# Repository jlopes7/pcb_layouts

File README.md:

# pcb_layouts
FOSS PCB Based layouts

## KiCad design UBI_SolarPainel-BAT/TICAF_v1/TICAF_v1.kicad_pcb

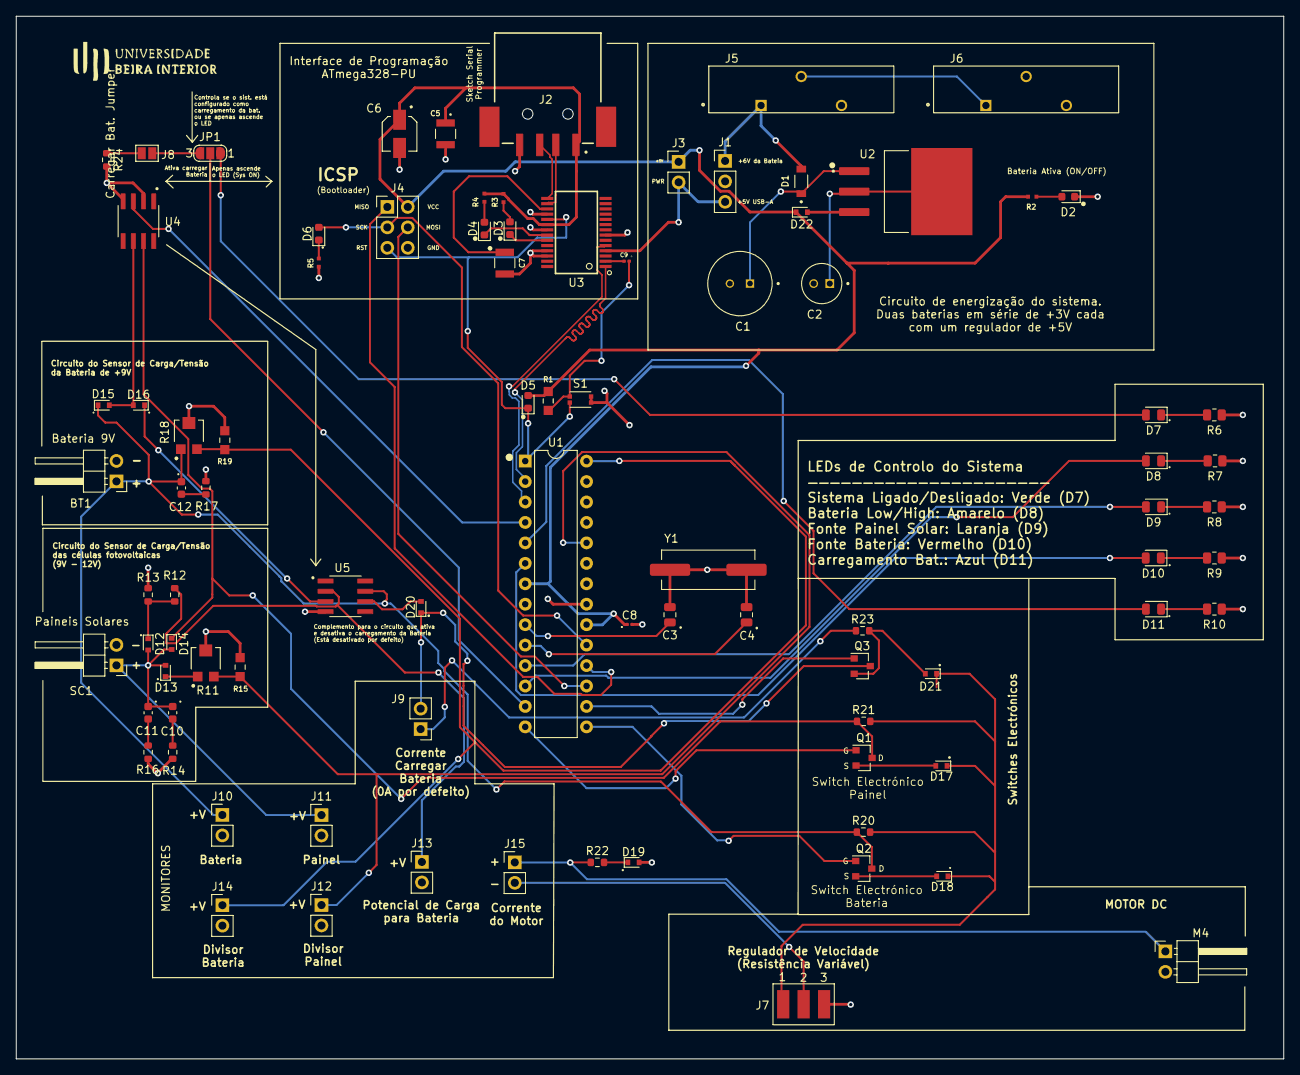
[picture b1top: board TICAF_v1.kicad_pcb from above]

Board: 2 copper layers, 157.5 x 129.5 mm, 87 parts (0 on the bottom side), 67 nets.

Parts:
BT1: Bateria 9V; PinHeader_1x02_P2.54mm_Horizontal
C1: 100u; CAPPRD250W45D800H500
C2: 27u; CAPPRD200W50D500H1100
C3, C4: 22p; C_0805_2012Metric
C5, C7: 0.1u; CAP_ECHU1C104GX5
C6: 10u; CAP_EEEFN0J100R
C8, C9: 100n; C_0201_0603Metric
C10, C12: 10u; C_0603_1608Metric
C11: 22u; C_0603_1608Metric
D1: RB160MM-30TR; DIO_RB160MM-30TR
D2, D3, D4, D6: LED; LED_0603_1608Metric
D5: DIODE; LED_0603_1608Metric
D7: Verde; LED_0805_2012Metric
D8: Amarelo; LED_0805_2012Metric
D9: Laranja; LED_0805_2012Metric
D10: Vermelho; LED_0805_2012Metric
D11: Azul; LED_0805_2012Metric
D12, D13, D14, D15, D16, D17, D18, D19, D20, D21, D22: D; D_SOD-523
J1: Conn_01x03_Male; PinHeader_1x03_P2.54mm_Vertical
J2: USB_A; SAMTEC_USB-A-S-X-X-SM2
J3: Conn_01x02_Male; PinHeader_1x02_P2.54mm_Vertical
J4: ICSP; PinHeader_2x03_P2.54mm_Vertical
J5: Bat Cell 1(3V); TE_1775485-2
J6: Bat Cell 2(3V); TE_1775485-2
J7: Regulador de Velocidade (Potentiometer); Power_Connector
J8: Carregar Bat. Jumper; SolderJumper-2_P1.3mm_Open_Pad1.0x1.5mm
J9: Hard Activate Jumper; PinHeader_1x02_P2.54mm_Vertical
J10: Monitor Bateria; PinHeader_1x02_P2.54mm_Vertical
J11: Monitor Painel; PinHeader_1x02_P2.54mm_Vertical
J12, J14: Monitor Div. Bateria; PinHeader_1x02_P2.54mm_Vertical
J13: Monitor Carrega Bateria; PinHeader_1x02_P2.54mm_Vertical
J15: Monitor Corrente Motor; PinHeader_1x02_P2.54mm_Vertical
JP1: Jumper_3_Bridged12; SolderJumper-3_P1.3mm_Open_RoundedPad1.0x1.5mm_NumberLabels
M4: Motor_DC; PinHeader_1x02_P2.54mm_Horizontal
Q1: Switch Painel; SOT-23-2
Q2: Switch Bateria; SOT-23-2
Q3: Switch Ch Bat; SOT-23-2
R1, R15, R19: 10k; RES_ERA6VRW1002V
R2: 220; RES_ERA2VEB2200X
R3, R4, R5: 220R; RES_ERA2VEB2200X
R6, R7, R8, R9: 150R; R_0805_2012Metric
R10: 422R; R_0805_2012Metric
R11, R18: 30k; TRIM_TC33X-2-303E
R12, R20, R21, R23: 100k; R_0603_1608Metric
R13, R14, R16, R17, R22, R24: 1k; R_0603_1608Metric
S1: BTN Reset; SW_EVPBB0AAB000
SC1: Paineis Solares; PinHeader_1x02_P2.54mm_Horizontal
U1: ATmega328-PU; DIP-28_W7.62mm
U2: LM7805S_NOPB; TO254P1524X483-4N
U3: FT232RL-REEL; SOP65P780X200-28N
U4, U5: TL972QDRQ1; SOIC127P599X175-8N
Y1: 16MHz; XTAL1140X490X430N

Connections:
+5V: C5.1, C6.1, C8.1, D5.2, D22.1, J2.01, J3.1, J4.2, R1.1, R2.1, R3.2, R4.1, U1.7, U1.20, U3.20
/+6VBAT: D1.A, J1.1, J5.1
/A1_328P_IN: J12.1, R11.3, R15.2, U1.24
/A5_328P_IN: J14.1, R18.3, R19.2, U1.28
/BCVGS: Q3.2, U1.16
/BVGS: Q2.2, U1.15
/Controlos Painel Solar / Bateria/+OP_CHARGE: D16.1, U5.3
/Controlos Painel Solar / Bateria/-OP_CHARGE: J13.1, R12.2, U5.2
/Controlos Painel Solar / Bateria/BTN_CHARGE_BAT: J8.1, JP1.3
/Controlos Painel Solar / Bateria/D_SWPAINEL: D14.1, Q1.1, R21.1, U4.7
/Controlos Painel Solar / Bateria/LED_Sys_ON: D7.2, JP1.1
/Controlos Painel Solar / Bateria/MONPAINELV: C10.1, C11.1, D12.2, D13.2, D14.2, J11.1, SC1.1
/Controlos Painel Solar / Bateria/Motor e Switches de Controlo/MOTOR_INPUT: D17.1, D18.1, D21.1, J7.1, R20.2, R21.2
/Controlos Painel Solar / Bateria/Motor e Switches de Controlo/SWITCH_BAT_CHARGE: D20.2, U5.6
/Controlos Painel Solar / Bateria/OP_CHARGE_OUT: D15.2, D16.2, U4.6
/Controlos Painel Solar / Bateria/SWBATPOT: BT1.1, C12.1, D15.1, J10.1, Q2.1, R18.1, R20.1, U5.7
/DTR: C9.2, U3.2
/DTR_328P: C9.1, R1.2, S1.A1
/L_BATON: D10.2, U1.6
/L_CHARGEBAT: D11.2, U1.5
/L_LOWBAT: D8.2, U1.12
/L_PAINELON: D9.2, U1.11
/L_SYSON: JP1.2, U1.13
/Módulo FTDI - USB to Serial/USB_D+: J2.03, U3.15
/Módulo FTDI - USB to Serial/USB_D-: J2.02, U3.16
/OPAMP_SIGNAL: U1.4, U4.3
/PVGS: Q1.2, U1.14
/PWR: J1.3, J3.2, U3.4
/TRXD+: U1.2, U3.1
/TRXD-: U1.3, U3.5
/VREG_OUT: D22.2, U2.3
GND: BT1.2, C1.N, C2.N, C3.2, C4.2, C5.2, C6.2, C7.2, C8.2, D2.1, D19.2, J1.2, J2.04, J4.6, J6.2, J7.3, J10.2, J11.2, J12.2, J13.2, J14.2, M4.2, R5.2, R6.1, R7.1, R8.1, R9.1, R10.1, R11.2, R13.2, R14.2, R15.1, R16.2, R17.2, R18.2, R19.1, R24.2, S1.B1, S1.B2, SC1.2, U1.8, U1.21, U1.22, U1.23, U1.25, U1.26, U3.7, U3.18, U3.21, U3.25, U3.26, U4.2, U4.4, U5.4, Y1.1, Y1.2
unnamed: C1.P, D1.K, U2.1
unnamed: C2.P, U2.2, U2.4
unnamed: C7.1, U3.17
unnamed: C10.2, R14.1
unnamed: C11.2, R16.1
unnamed: C12.2, R17.1
unnamed: D2.2, R2.2
unnamed: D3.1, U3.23
unnamed: D3.2, R3.1
unnamed: D4.1, U3.22
unnamed: D4.2, R4.2
unnamed: D6.1, R5.1
unnamed: D6.2, J4.3, U1.19
unnamed: D7.1, R6.2
unnamed: D8.1, R7.2
unnamed: D9.1, R8.2
unnamed: D10.1, R9.2
unnamed: D11.1, R10.2
unnamed: D12.1, R12.1, R13.1
unnamed: D13.1, R11.1
unnamed: D17.2, Q1.3
unnamed: D18.2, Q2.3
unnamed: D19.1, R22.2
unnamed: D20.1, J9.2, Q3.1
unnamed: D21.2, Q3.3, R23.2
unnamed: J4.1, U1.18
unnamed: J4.4, U1.17
unnamed: J5.2, J6.1
unnamed: J8.2, R24.1
unnamed: J9.1, R23.1
unnamed: J15.1, M4.1, R22.1
unnamed: J7.2, J15.2
RESET: D5.1, J4.5, S1.A2, U1.1, U3.19
XTAL1_328P: C3.1, U1.9
XTAL2_328P: C4.1, U1.10

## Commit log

2022-01-03 First Version
2022-01-03 Changed the name of the folder
2022-01-03 Fixed the missing INO folder
2022-01-03 Added the missing Kicad libraries
2022-01-03 Added the missing libraries
2022-01-03 Removed the *.lib constraints
